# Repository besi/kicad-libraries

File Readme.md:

# Kicad Libraries

    git submodule add https://github.com/besi/kicad-esp8266             lib/esp8266
    git submodule add https://github.com/besi/kicad-tp4056              lib/tp4056
    git submodule add https://github.com/besi/kicad-lilygo-sim          lib/lilygo-sim
    git submodule add https://github.com/besi/kicad-relais-module       lib/relais-module
    git submodule add https://github.com/besi/kicad-esp-01m             lib/esp-01m
    git submodule add https://github.com/besi/kicad-radio-receiver      lib/radio-receiver
    git submodule add https://github.com/besi/kicad-dcdc                lib/dcdc
    git submodule add https://github.com/besi/kicad-schurter-switch     lib/schurter-switch
    git submodule add https://github.com/besi/kicad-mems-mic            lib/mems-mic
    git submodule add https://github.com/besi/kicad-neopixel-strip      lib/neopixel-strip
    git submodule add https://github.com/besi/kicad-ftdi-connector      lib/ftdi-connector
    git submodule add https://github.com/besi/kicad-c8-inlet            lib/c8-inlet
    git submodule add https://github.com/besi/kicad-rdm-6300            lib/rdm-6300
    git submodule add https://github.com/besi/kicad-magnetic-charger    lib/magnetic-charger
    git submodule add https://github.com/besi/kicad-sd-card             lib/sd-card
    git submodule add https://github.com/besi/kicad-adafruit-MAX98357   lib/adafruit-MAX98357
    git submodule add https://github.com/besi/kicad-lxb18               lib/lxb18
    git submodule add https://github.com/besi/kicad-rcj-22              lib/rcj-22
    git submodule add https://github.com/besi/kicad-midi                lib/midi
    git submodule add https://github.com/besi/kicad-esp32-wemos-d1-mini lib/esp32-wemos-d1-mini
    git submodule add https://github.com/besi/kicad-tcrt5000            lib/tcrt5000
    git submodule add https://github.com/besi/kicad-usb-a-pcb           lib/usb-a-pcb
    git submodule add https://github.com/besi/kicad-tcnd5000            lib/tcnd5000
    git submodule add https://github.com/besi/kicad-max98367            lib/max98367
    git submodule add https://github.com/besi/kicad-esp-01f             lib/esp-01f    
    git submodule add https://github.com/besi/kicad-bme280              lib/bme280
    git submodule add https://github.com/besi/kicad-m18                 lib/m18
    git submodule add https://github.com/besi/kicad-dd1718pa            lib/dd1718pa
    git submodule add https://github.com/besi/kicad-opb607a             lib/opb607a
    git submodule add https://github.com/besi/kicad-molex-poe           lib/molex-poe
    git submodule add https://github.com/besi/kicad-as12ap              lib/as12ap
    git submodule add https://github.com/besi/kicad-charge-module       lib/charge-module
    git submodule add https://github.com/besi/kicad-ld2450              lib/ld2450
    git submodule add https://github.com/besi/kicad-c3-pico             lib/c3-pico
    git submodule add https://github.com/besi/kicad-qwiic-adapter       lib/qwiic-adapter
    git submodule add https://github.com/besi/kicad-dcf77               lib/dcf77
    git submodule add https://github.com/besi/kicad-28byj               lib/28byj
    git submodule add https://github.com/besi/kicad-pts636              lib/pts636
    git submodule add https://github.com/besi/kicad-iec320-c14          lib/iec320-c14
    git submodule add https://github.com/besi/kicad-c14-outlet          lib/c14-outlet
    git submodule add https://github.com/besi/kicad-tpa3110             lib/tpa3110
    git submodule add https://github.com/besi/kicad-hw357               lib/hw357
    git submodule add https://github.com/besi/kicad-uda1334             lib/uda1334
    
Synchronise the git submodules

    git submodule update --init --recursive

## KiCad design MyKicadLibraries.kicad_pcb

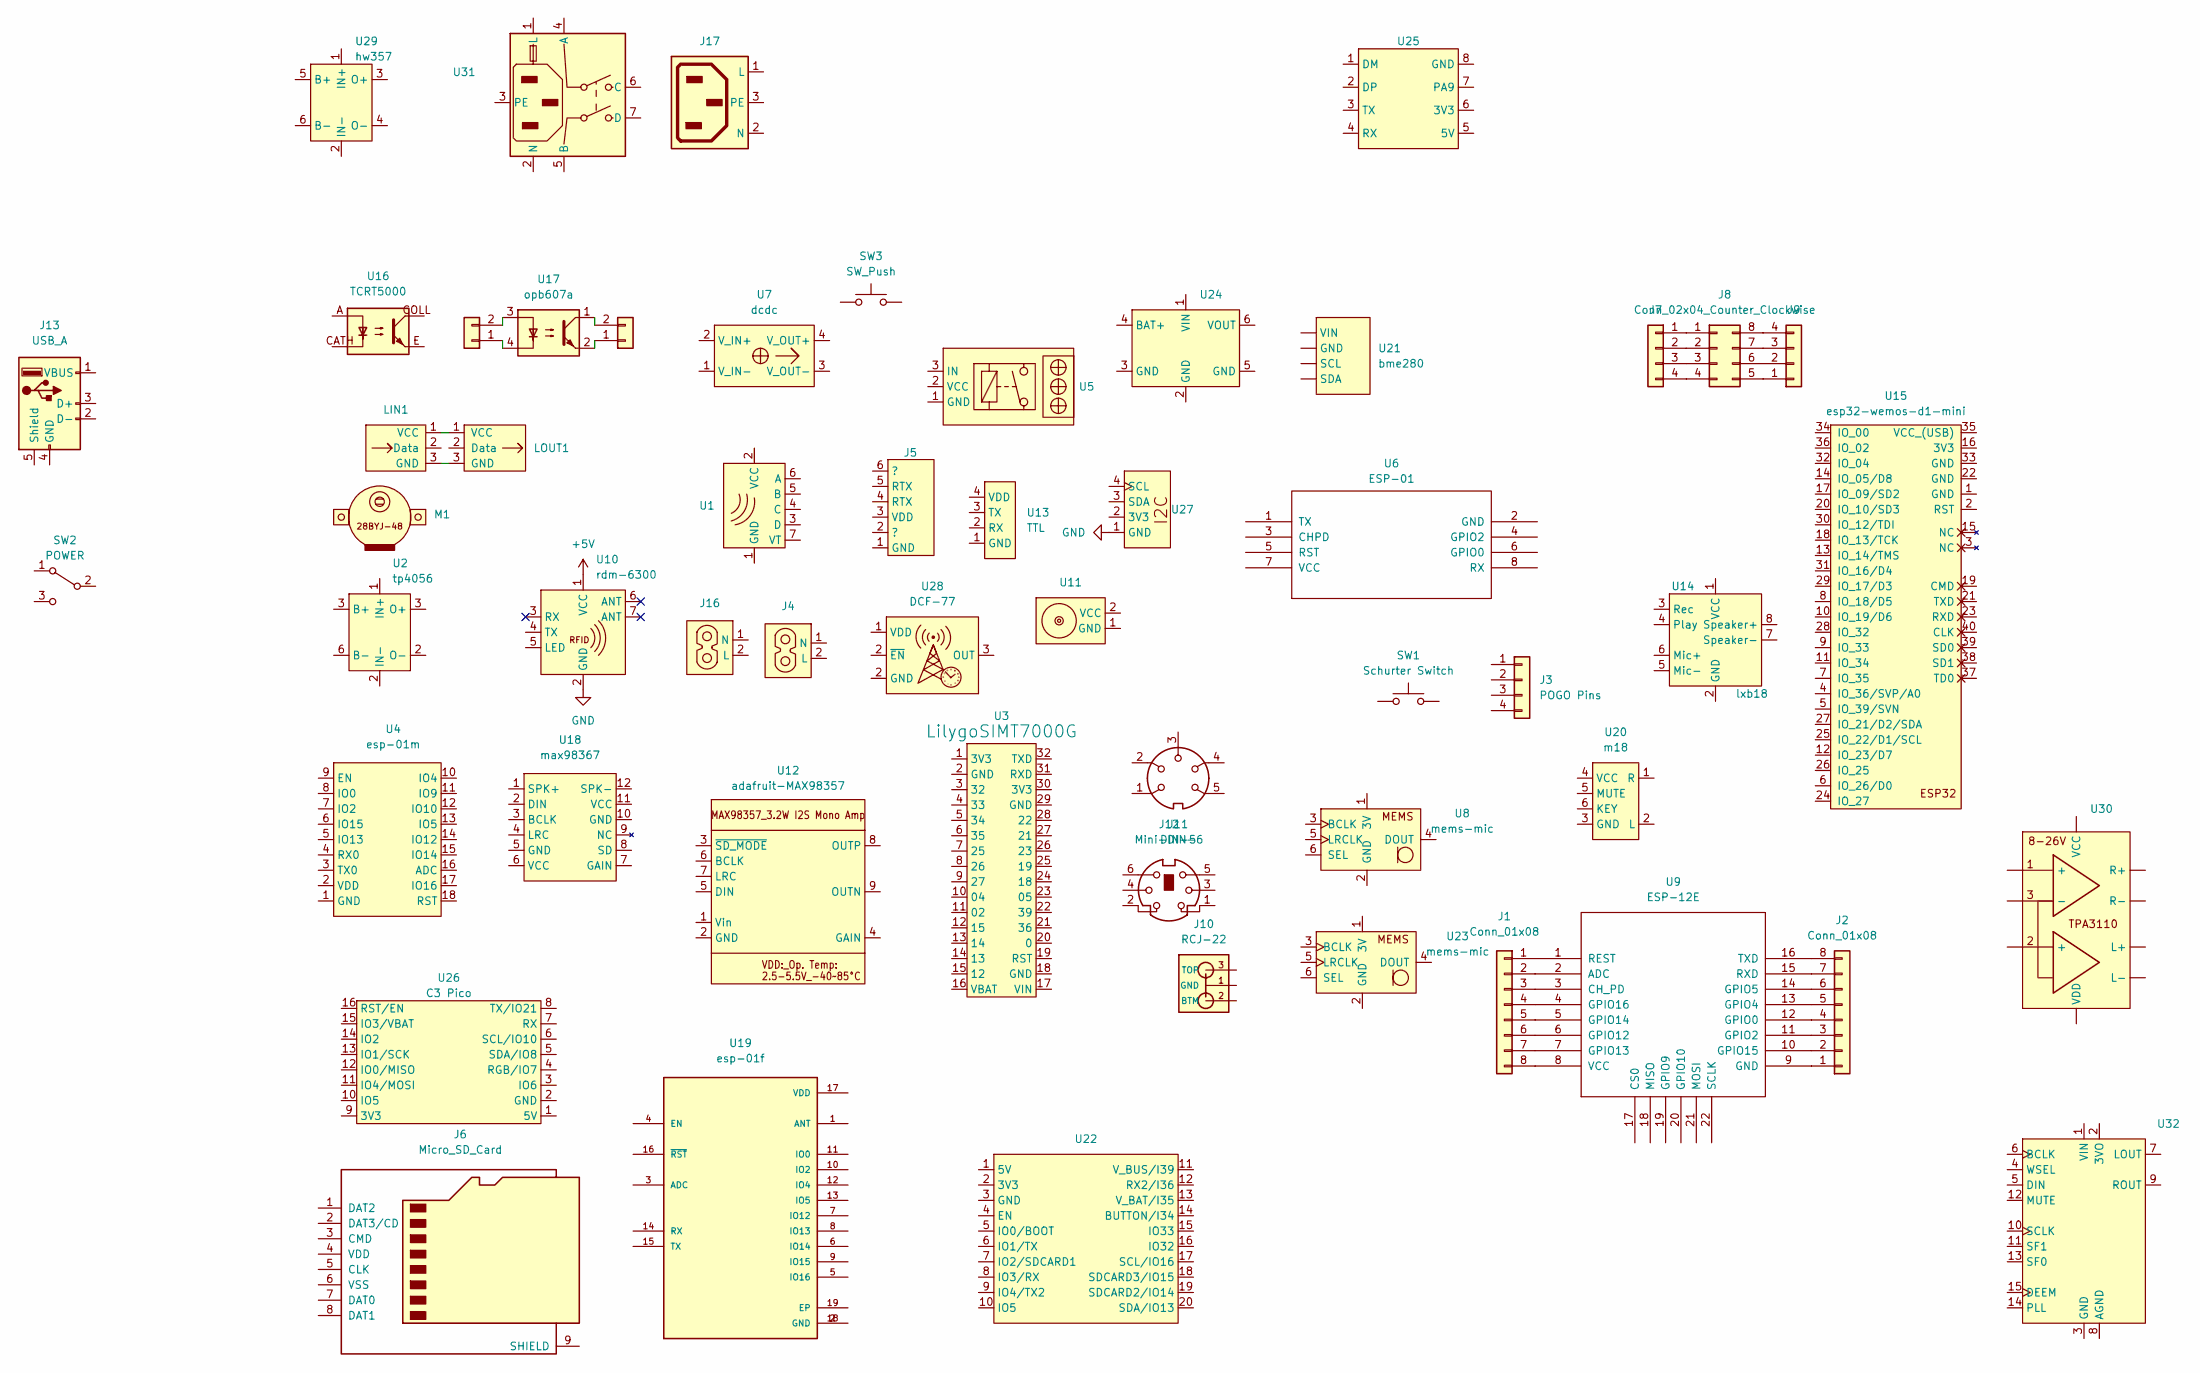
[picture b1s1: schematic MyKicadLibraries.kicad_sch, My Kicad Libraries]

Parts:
J1, J2: Conn_01x08; PinHeader_1x08_P2.54mm_Vertical
J3: POGO Pins; magnetic-pogo
J4: c8-inlet
J5: FTDI; PinHeader_1x06_P2.54mm_Horizontal
J6: Micro_SD_Card; sd-card
J7, J9: Conn_01x04; PinHeader_1x04_P2.54mm_Vertical
J8: Conn_02x04_Counter_Clockwise; SOIC-8_3.9x4.9mm_P1.27mm
J10: RCJ-22; rcj-22
J11: DIN-5; midi
J12: Mini-DIN-6; midi-din6
J13: USB_A; usb-a-pcb
J14, J15: Conn_01x02; PinHeader_1x02_P2.54mm_Vertical
J16: c8-inlet; c8-inlet-old
J17: c14-outlet
LIN1: LEDs_In; neopixel-strip
LOUT1: LEDs_Out; neopixel-strip
M1: 28byj
SW1: Schurter Switch; schurter-switch
SW2: POWER; as12ap
SW3: SW_Push; pts636
U1: radio-receiver
U2: tp4056
U3: LilygoSIMT7000G; LilygoSIM7000G
U4: esp-01m
U5: relais_module
U6: ESP-01
U7: dcdc
U8: mems-mic
U9: ESP-12E
U10: rdm-6300
U11: magnetic-charger
U12: adafruit-MAX98357
U13: TTL; PinHeader_1x04_P2.54mm_Vertical
U14: lxb18
U15: esp32-wemos-d1-mini
U16: TCRT5000; tcrt5000
U17: opb607a
U18: max98367
U19: esp-01f
U20: m18
U21: bme280
U22: molex-poe
U23: mems-mic; mems-mic-round
U24: charge-module
U25: ld2450
U26: C3 Pico; c3-pico
U27: qwiic-adapter
U28: DCF-77; dcf77
U29: hw357
U30: tpa3110
U31: iec320-c14
U32: uda1334

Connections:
+5V: U10.1 (VCC)
GND: U10.2 (GND), U27.1 (GND)
unnamed: J1.1, U9.1 (REST)
unnamed: J1.2, U9.2 (ADC)
unnamed: J1.3, U9.3 (CH_PD)
unnamed: J1.4, U9.4 (GPIO16)
unnamed: J1.5, U9.5 (GPIO14)
unnamed: J1.6, U9.6 (GPIO12)
unnamed: J1.7, U9.7 (GPIO13)
unnamed: J1.8, U9.8 (VCC)
unnamed: J2.1, U9.9 (GND)
unnamed: J2.2, U9.10 (GPIO15)
unnamed: J2.3, U9.11 (GPIO2)
unnamed: J2.4, U9.12 (GPIO0)
unnamed: J2.5, U9.13 (GPIO4)
unnamed: J2.6, U9.14 (GPIO5)
unnamed: J2.7, U9.15 (RXD)
unnamed: J2.8, U9.16 (TXD)
unnamed: J7.1, J8.1
unnamed: J7.2, J8.2
unnamed: J7.3, J8.3
unnamed: J7.4, J8.4
unnamed: J8.5, J9.1
unnamed: J8.6, J9.2
unnamed: J8.7, J9.3
unnamed: J8.8, J9.4
unnamed: J14.1, U17.4
unnamed: J14.2, U17.3
unnamed: J15.1, U17.2
unnamed: J15.2, U17.1
unnamed: LIN1.3 (GND), LOUT1.3 (GND)
unnamed: LIN1.1 (VCC), LOUT1.1 (VCC)
unnamed: U19.2 (GND), U19.18 (GND)

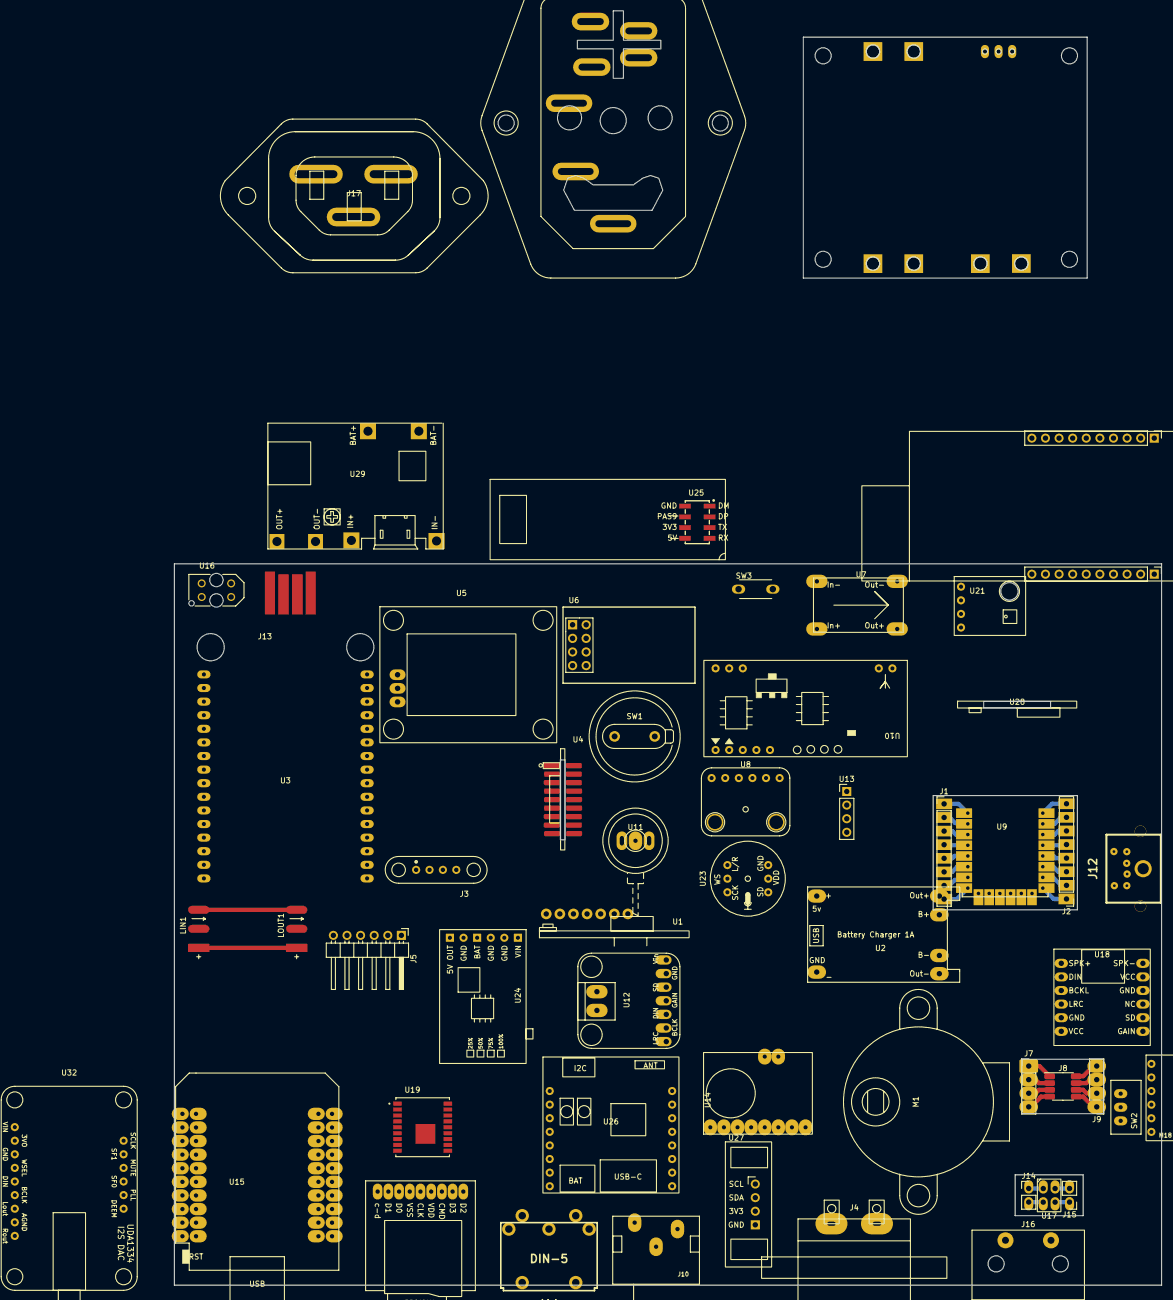
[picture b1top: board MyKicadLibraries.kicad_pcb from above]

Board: 2 copper layers, 184.4 x 134.7 mm, 55 parts (0 on the bottom side), 32 nets.

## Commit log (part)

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2022-12-18 Initial commit with the current submodules
2022-12-18 Add schematic items and the footprints
2022-12-18 Add dcdc module and add a breakout board
2022-12-18 Finish break out board
2022-12-19 Add project
2022-12-19 Add ESP-01m library
2022-12-19 Add neopixel library
2022-12-19 Update neopixel library
2022-12-19 Update url of neoipxel library
2022-12-29 Add mems mic
2022-12-29 Add schurter switch module
2022-12-29 Add magnetic pogo library
2023-01-01 Add FTDI connector
2023-01-11 Add new modules
2023-01-11 add round magnetic charger and update the libraries
2023-01-12 add sdcard module
2023-01-13 Update magnetic charger plug and sd card module
2023-02-19 Update TTL symbol
2023-02-19 Update modules
2023-02-24 Update tp4056 footprint
2023-04-25 Add SOIC8 breakout
2023-04-30 Add rcj-22 plug as well as lxb18 module
2023-05-03 Update rcj-22 module
2023-05-03 Add midi connector
2023-05-03 Add din6 midi plug
2023-11-16 Update submodules
2023-11-24 Add midi module
2023-11-24 Make sure libraries are checked in
2023-11-24 Add both the symbol as well as the footprint libraries to git
2023-11-28 Add readme
2023-11-28 Add USB pcb trace footprint
2023-12-03 Add TCND5000 Library
2023-12-04 Add OPB607A IR module
2023-12-12 Add OPB607a breakout
2023-12-12 New plot directory
2023-12-12 Update I2S amp Footprint
2023-12-12 Add MAX98367 footprint
2023-12-12 Update ESP01m footprint
2023-12-14 Add ESP-01F footprint
2023-12-14 Update ESP-01F module
2023-12-15 Describe how to synchronise the git modules
2023-12-23 Update ESP01m library
2024-01-22 Add BME280 sensor
2024-01-22 diff Update clearance
2024-01-26 Update tp4056 and fix edge cut issues
2024-01-26 Add m18 bluetooth module
2024-01-26 Add bme280 submodule
2024-02-08 Update main file
2024-02-21 Add edge components to the edge
2024-03-04 Add molex poe footprint
2024-03-04 Update mems mic and adafruit i2s amp
2024-03-04 Update mems mic
2024-03-08 Add as12ap
2024-03-10 Update radio receiver footprint
2024-03-14 Prepare adding the pogo connectors
2024-03-14 Add charge module
2024-03-15 Add lipo charger module
2024-04-02 Fix mems-mic pin assignment
2024-04-02 Add screenshot
2024-04-19 Add ld2450
2024-12-03 Add Lolin C3 Footprint
2024-12-04 Update Lolin c3 pico component
2025-02-04 Add QWIIC adapter
2025-02-10 Add DCF77
2025-02-18 Update radio module RX480E
2025-03-07 Update c8 footprint
2025-03-07 Update ESP01m
2025-03-07 Add missing c3-pico module
2025-03-07 Add missing reference for the qwiic adapter
2025-03-12 Add 28byj stepper motor footprint
2025-03-14 Update DCF77 library
2025-03-14 Fix in DCF77 library
2025-03-31 Add PTS636
2025-12-11 Update C3 library
2025-12-11 Formatting in Readme
2026-01-19 Add hw357 boost converter
2026-01-27 Add preliminary IEC320-C14 footprint
2026-01-27 Add IEC320-C14 power inlet
2026-01-27 Update the Readme with IEC320-C14 power inlet
2026-01-27 Add C14 outline
2026-01-28 Add TPA3110 amplifier footprint
2026-01-29 Update footprint libraries
2026-01-29 Update C14 footprint
2026-04-02 Add the missing hw357 module to the readme
2026-04-02 Update the magnetic-connector footprint
2026-04-15 Add lolin32 footprint
